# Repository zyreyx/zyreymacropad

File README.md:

# zyreymacropad
Hackpad for Hackclub!

## 3D Model

Heres the image of the entire hackpad, sorry about the cyan keycap tops the 3d model that was linked came like that and I couldn't fix it.

## PCB

# Assembly 

One M3x16mm screw will be placed into each red circled hole 

## Part List

PCB
9 MX-Style switches

1 Seeed XIAO RP2040

9 Through-hole 1N4148 Diodes

9 Blank DSA keycaps

4 M3x16mm screws

3D Printed Case

# Sorry its not very advanced, this was my first project but I'm proud of it (:

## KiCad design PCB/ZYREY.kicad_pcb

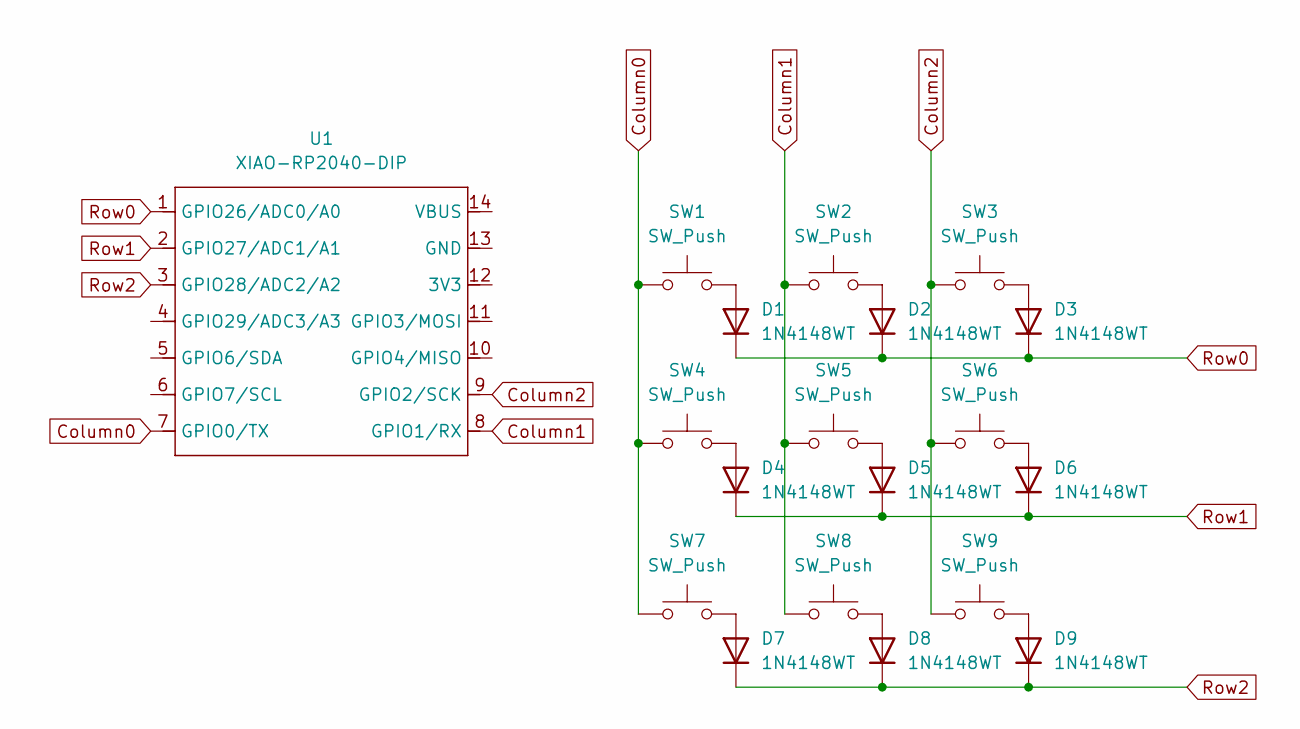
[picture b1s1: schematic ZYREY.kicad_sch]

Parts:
D1, D2, D3, D4, D5, D6, D7, D8, D9: 1N4148WT; D_SOD-523
SW1, SW2, SW3, SW4, SW5, SW6, SW7, SW8, SW9: SW_Push; SW_Cherry_MX_1.00u_PCB
U1: XIAO-RP2040-DIP

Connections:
Column0: SW1.1, SW4.1, SW7.1, U1.7 (GPIO0/TX)
Column1: SW2.1, SW5.1, SW8.1, U1.8 (GPIO1/RX)
Column2: SW3.1, SW6.1, SW9.1, U1.9 (GPIO2/SCK)
unnamed: D1.2 (A), SW1.2
unnamed: D2.2 (A), SW2.2
unnamed: D3.2 (A), SW3.2
unnamed: D4.2 (A), SW4.2
unnamed: D5.2 (A), SW5.2
unnamed: D6.2 (A), SW6.2
unnamed: D7.2 (A), SW7.2
unnamed: D8.2 (A), SW8.2
unnamed: D9.2 (A), SW9.2
Row0: D1.1 (K), D2.1 (K), D3.1 (K), U1.1 (GPIO26/ADC0/A0)
Row1: D4.1 (K), D5.1 (K), D6.1 (K), U1.2 (GPIO27/ADC1/A1)
Row2: D7.1 (K), D8.1 (K), D9.1 (K), U1.3 (GPIO28/ADC2/A2)

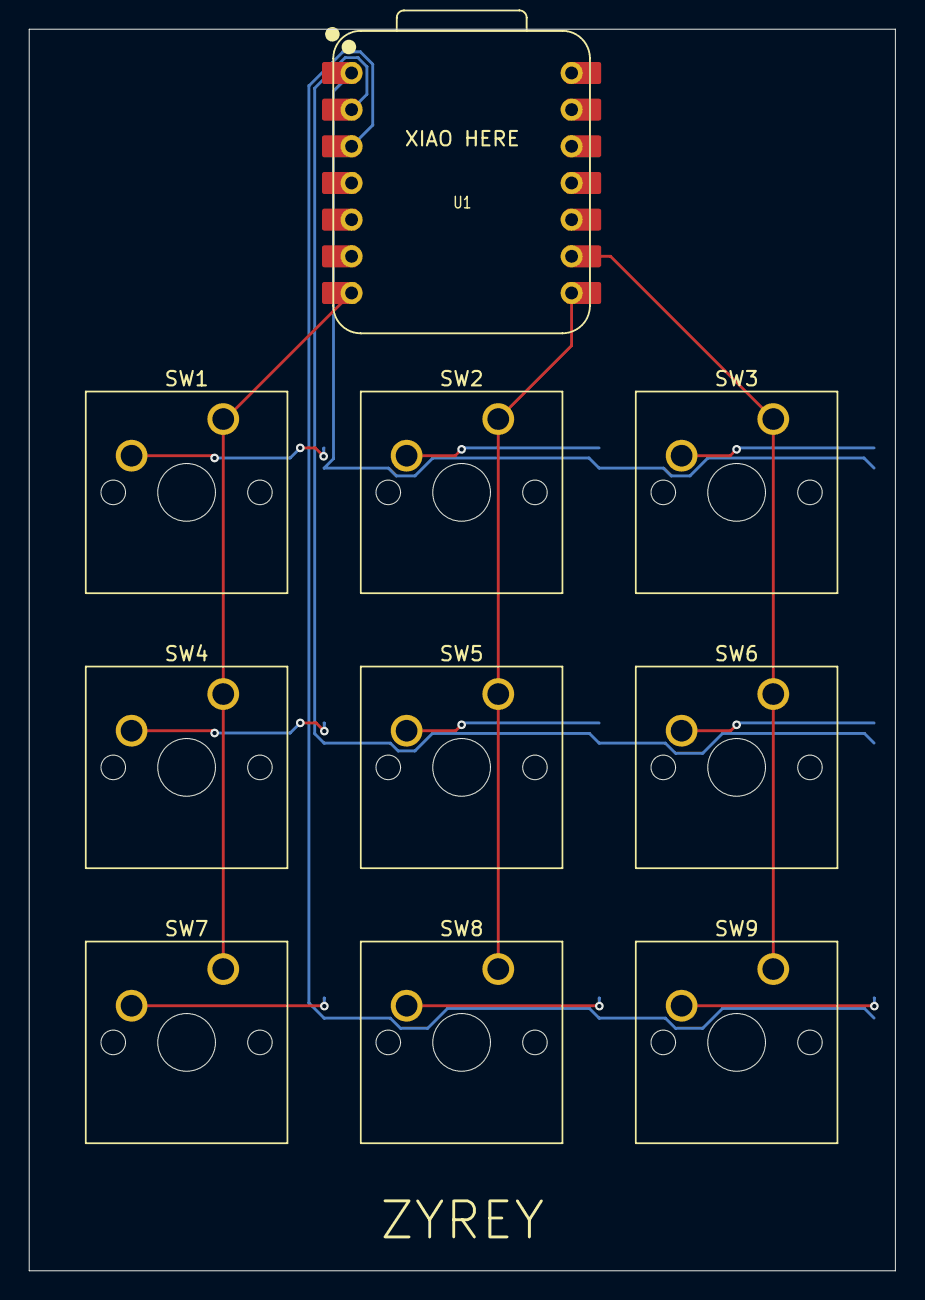
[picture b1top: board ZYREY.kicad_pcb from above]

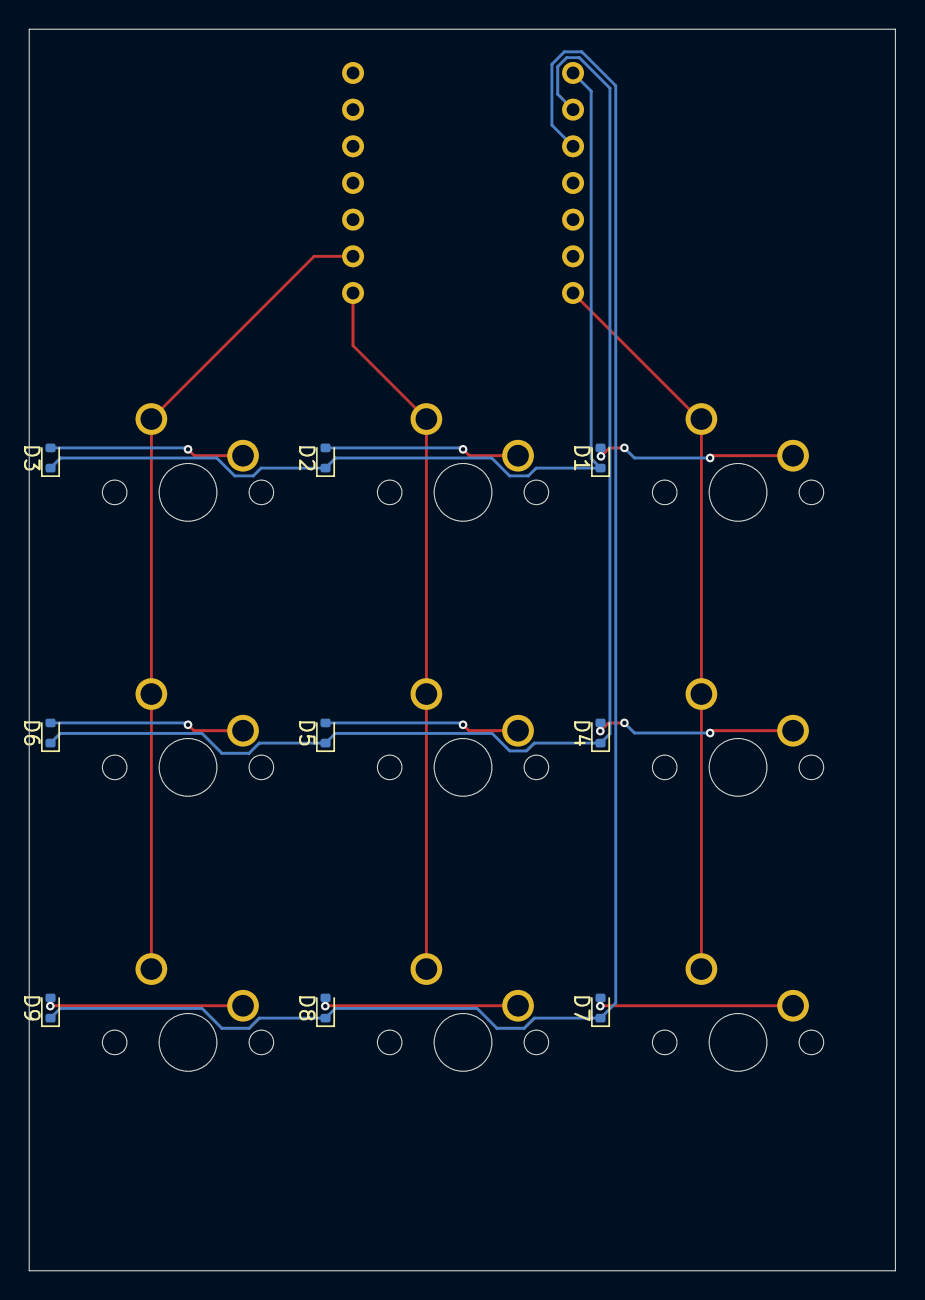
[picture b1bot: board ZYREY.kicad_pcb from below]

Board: 2 copper layers, 60.0 x 86.0 mm, 19 parts (9 on the bottom side), 15 nets.

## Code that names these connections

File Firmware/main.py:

import board
from kmk.kmk_keyboard import KMKKeyboard
from kmk.keys import KC
from kmk.modules.macros import Press, Release, Tap, Macros

keyboard = KMKKeyboard()
macros = Macros()
keyboard.modules.append(macros)

keyboard.col_pins = (board.D1, board.D2, board.D3)  # Column0, Column1, Column2
keyboard.row_pins = (board.D4, board.D6, board.D7)  # Row0, Row1, Row2
keyboard.diode_orientation = 'COL2ROW'

keyboard.keymap = [
    [
        # Top row 
        KC.F1,                             
        KC.F2,
        KC.F3,
        
        # Middle row 
        KC.MACRO("your.email@example.com"),
        KC.MACRO("0211234567"),              
        KC.PIPE,                            
        
        # Bottom row 
        KC.AUDIO_VOL_DOWN,
        KC.AUDIO_MUTE,
        KC.AUDIO_VOL_UP,
    ]
]

if __name__ == '__main__':
    keyboard.go()

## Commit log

2025-12-07 Update README with project details and images
    Added sections for 3D model, schematic, PCB, assembly, and part list.
2025-12-10 Update README with new PCB and Assembly images
    Added new images for PCB and Assembly sections in README.
